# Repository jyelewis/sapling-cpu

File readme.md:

## Sapling CPU

Commands
 - `make test`
 - `make run-sam SAM=pkg6_software/hello.sam`
 - `make run-sam SAM=pkg6_software/primes.sam`

Viewing waveforms
 - `uv run pytest pkg3_cpu_hdl/testbench/test_testbench.py`
 - `surfer build/cocotb/testbench/testbench.fst`

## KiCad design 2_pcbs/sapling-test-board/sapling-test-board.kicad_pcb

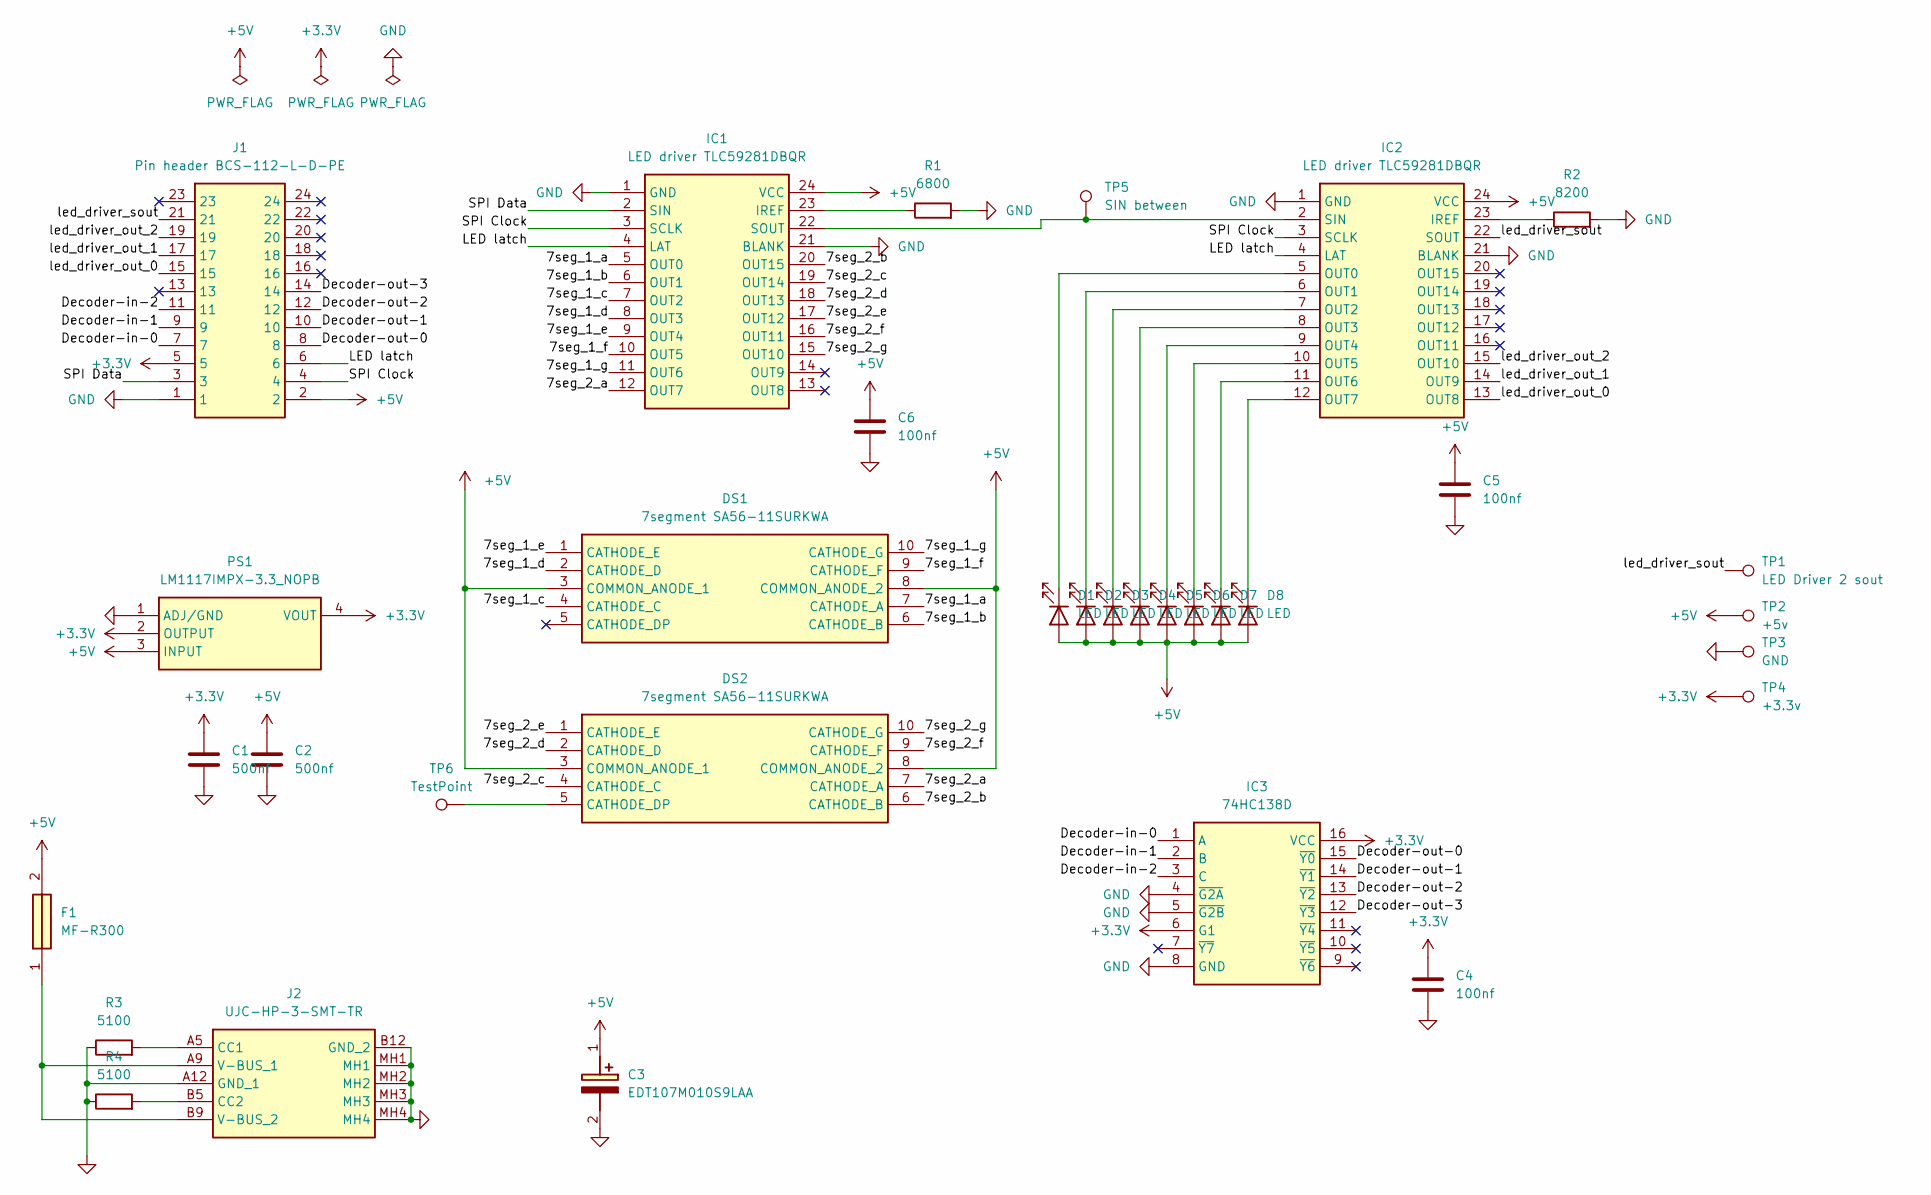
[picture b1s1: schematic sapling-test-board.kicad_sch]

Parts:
C1, C2: 500nf; C_0805_2012Metric
C3: EDT107M010S9LAA; CAPAE830X650N; Mouser Part Number 80-EDT107M010S9LAA
C4, C5, C6: 100nf; C_0805_2012Metric
D1, D2, D3, D4, D5, D6, D7, D8: LED; LED_D5.0mm
DS1, DS2: 7segment SA56-11SURKWA; DIPS1524W75P254L1270H825Q10N; Mouser Part Number 604-SA56-11CGKWA
F1: MF-R300; MFR300; Mouser Part Number 652-MFR300
IC1, IC2: LED driver TLC59281DBQR; SOP64P600X175-24N; Mouser Part Number 595-TLC59281DBQR
IC3: 74HC138D; SOIC127P600X175-16N; Mouser Part Number 757-74HC138D
J1: Pin header BCS-112-L-D-PE; BCS-112-XXX-D-PE; Mouser Part Number 200-BCS112LDPE
J2: UJC-HP-3-SMT-TR; UJCHP3SMTTR; Mouser Part Number 490-UJC-HP-3-SMT-TR
PS1: LM1117IMPX-3.3_NOPB; SOT230P700X180-4N; Mouser Part Number 926-LM1117IMPX33NOPB
R1: 6800; R_0805_2012Metric
R2: 8200; R_0805_2012Metric
R3, R4: 5100; R_0805_2012Metric
TP1: LED Driver 2 sout; TestPoint_Pad_D4.0mm
TP2: +5v; TestPoint_Pad_D4.0mm
TP3: GND; TestPoint_Pad_D4.0mm
TP4: +3.3v; TestPoint_Pad_D4.0mm
TP5: SIN between; TestPoint_Pad_D4.0mm
TP6: TestPoint; TestPoint_Pad_D4.0mm

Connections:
+3.3V: C1.2, C4.2, IC3.6 (G1), IC3.16 (VCC), J1.5, PS1.2 (OUTPUT), PS1.4 (VOUT), TP4.1 (1_1)
+5V: C2.2, C3.1 (+), C5.2, C6.2, D1.2 (A), D2.2 (A), D3.2 (A), D4.2 (A), D5.2 (A), D6.2 (A), D7.2 (A), D8.2 (A), DS1.3 (COMMON_ANODE_1), DS1.8 (COMMON_ANODE_2), DS2.3 (COMMON_ANODE_1), DS2.8 (COMMON_ANODE_2), F1.2, IC1.24 (VCC), IC2.24 (VCC), J1.2, PS1.3 (INPUT), TP2.1 (1_1)
/7seg_1_a: DS1.7 (CATHODE_A), IC1.5 (OUT0)
/7seg_1_b: DS1.6 (CATHODE_B), IC1.6 (OUT1)
/7seg_1_c: DS1.4 (CATHODE_C), IC1.7 (OUT2)
/7seg_1_d: DS1.2 (CATHODE_D), IC1.8 (OUT3)
/7seg_1_e: DS1.1 (CATHODE_E), IC1.9 (OUT4)
/7seg_1_f: DS1.9 (CATHODE_F), IC1.10 (OUT5)
/7seg_1_g: DS1.10 (CATHODE_G), IC1.11 (OUT6)
/7seg_2_a: DS2.7 (CATHODE_A), IC1.12 (OUT7)
/7seg_2_b: DS2.6 (CATHODE_B), IC1.20 (OUT15)
/7seg_2_c: DS2.4 (CATHODE_C), IC1.19 (OUT14)
/7seg_2_d: DS2.2 (CATHODE_D), IC1.18 (OUT13)
/7seg_2_e: DS2.1 (CATHODE_E), IC1.17 (OUT12)
/7seg_2_f: DS2.9 (CATHODE_F), IC1.16 (OUT11)
/7seg_2_g: DS2.10 (CATHODE_G), IC1.15 (OUT10)
/Decoder-in-0: IC3.1 (A), J1.7
/Decoder-in-1: IC3.2 (B), J1.9
/Decoder-in-2: IC3.3 (C), J1.11
/Decoder-out-0: IC3.15 (~Y0), J1.8
/Decoder-out-1: IC3.14 (~Y1), J1.10
/Decoder-out-2: IC3.13 (~Y2), J1.12
/Decoder-out-3: IC3.12 (~Y3), J1.14
/LED latch: IC1.4 (LAT), IC2.4 (LAT), J1.6
/SPI Clock: IC1.3 (SCLK), IC2.3 (SCLK), J1.4
/SPI Data: IC1.2 (SIN), J1.3
/led_driver_out_0: IC2.13 (OUT8), J1.15
/led_driver_out_1: IC2.14 (OUT9), J1.17
/led_driver_out_2: IC2.15 (OUT10), J1.19
/led_driver_sout: IC2.22 (SOUT), J1.21, TP1.1 (1_1)
GND: C1.1, C2.1, C3.2 (-), C4.1, C5.1, C6.1, IC1.1 (GND), IC1.21 (BLANK), IC2.1 (GND), IC2.21 (BLANK), IC3.4 (~G2A), IC3.5 (~G2B), IC3.8 (GND), J1.1, J2.A12 (GND_1), J2.B12 (GND_2), J2.MH1, J2.MH2, J2.MH3, J2.MH4, PS1.1 (ADJ/GND), R1.2, R2.2, R3.1, R4.1, TP3.1 (1_1)
unnamed: D1.1 (K), IC2.5 (OUT0)
unnamed: D2.1 (K), IC2.6 (OUT1)
unnamed: D3.1 (K), IC2.7 (OUT2)
unnamed: D4.1 (K), IC2.8 (OUT3)
unnamed: D5.1 (K), IC2.9 (OUT4)
unnamed: D6.1 (K), IC2.10 (OUT5)
unnamed: D7.1 (K), IC2.11 (OUT6)
unnamed: D8.1 (K), IC2.12 (OUT7)
unnamed: DS2.5 (CATHODE_DP), TP6.1 (1_1)
unnamed: IC1.23 (IREF), R1.1
unnamed: IC1.22 (SOUT), IC2.2 (SIN), TP5.1 (1_1)
unnamed: IC2.23 (IREF), R2.1
unnamed: J2.A5 (CC1), R3.2
unnamed: J2.B5 (CC2), R4.2
unnamed: F1.1, J2.A9 (V-BUS_1), J2.B9 (V-BUS_2)

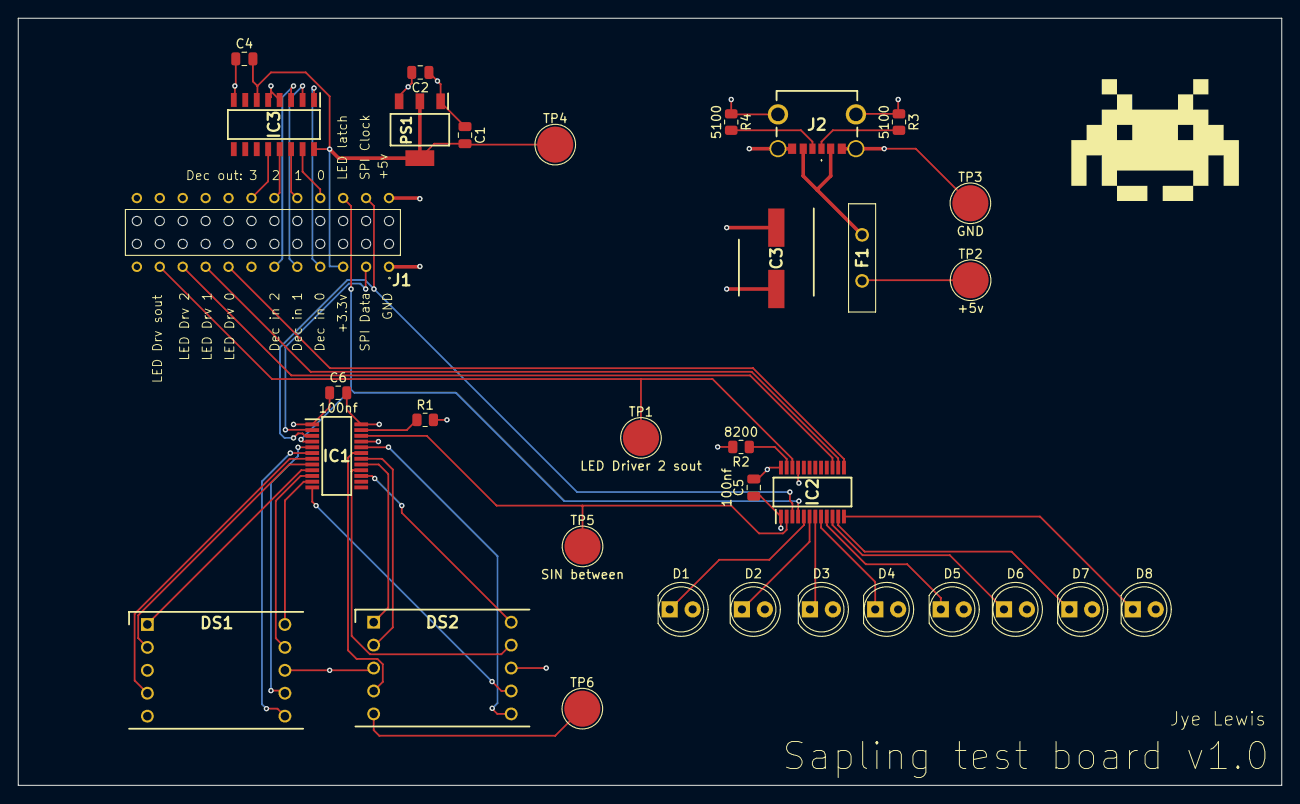
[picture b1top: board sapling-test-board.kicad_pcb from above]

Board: 4 copper layers, 140.0 x 85.0 mm, 33 parts (0 on the bottom side), 46 nets.

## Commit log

2026-04-19 ICEsugar top file & flash commands
2026-04-19 Structure to program different boards with unique IO
2026-04-19 Module: IceSugar_pmod_LEDs
2026-04-19 Module: clock_divider
2026-04-19 Tests
2026-04-19 Cleaned up clock divider edge cases
2026-04-19 SB_GB, github actions
2026-04-20 Components test board
2026-04-20 Auto routed PCB
2026-04-22 Hand routed PCB
2026-04-22 BB PCB review
2026-04-22 ISA instruction segments
2026-04-22 ISA documentation
2026-04-22 Documentation review + tidy up
2026-04-22 Silkscreen
2026-04-22 Test board PCB ordered
2026-04-23 Super basic assembler
2026-04-23 Assembler file outputs
2026-04-23 This is claudes codebase now
2026-04-23 Implement carry modes into assembler
2026-04-23 Implement carry modes into vm
2026-04-23 Another SAM example file
2026-04-23 Clean up the assembler & vm
2026-04-23 Clean up project structure, support #includes
2026-04-23 Break .PHONY blocks apart in makefile
2026-04-23 fmt, move into prefixed sub-dirs
2026-04-23 Remove custom pytest paths
2026-04-25 sapling_cpu_core module & minimal testbench
2026-04-25 Clean up, memory interface needs more thought
2026-04-26 Clean up tb_memory_controller tests
2026-04-26 tb_memory_controller
2026-04-26 Disable TB waves until we can solve for block memory
2026-04-26 test tb_memory_controller writes
2026-04-26 program_counter, test utils
2026-04-26 Fix closure bugs
2026-04-26 More test util clean up
2026-04-26 custom defines in tests, dramatically sped up tb_memory_controller by using packed arrays
2026-04-26 tb_memory_controller is now clocked
2026-04-26 Instruction register
2026-04-26 Instruction decoder
2026-04-26 types package
2026-04-26 Lots-o-wiring-up
2026-04-26 show_waveform() test decorator
2026-04-26 Respect memory stalls
2026-04-26 Always keep next_pc ahead so we're always fetching instructions
2026-04-26 Register bank
2026-04-27 Successfully loading imm8s
2026-04-27 Executing NOPs on FPGA
2026-04-27 VM endianness comments
2026-04-27 LOAD_REG_REG instruction
2026-04-27 Pretty messy but moving towards control signals, also load_reg_reg now works
2026-04-27 Disable waveform in test
2026-04-28 comments
2026-04-28 Split more cleanly into 3 pipeline stages
2026-04-28 Remove old comments
2026-04-28 LOAD_REG_MEM_ABSOLUTE instruction, first microcode step
2026-04-28 Clean up control unit
2026-04-29 STORE_MEM_ABSOLUTE_REG - broken
2026-04-29 STORE_MEM_ABSOLUTE_REG - fixed
2026-04-29 Scaffold ALU
2026-05-02 Complete ALU (not integrated yet)
2026-05-02 Test board pin out
2026-05-03 Messy but functional test board controller
2026-05-03 Integrate ALU, implement ADD opcode (no carry)
2026-05-03 Implement ALU carry
2026-05-04 Implement the rest of the ALU ops, SP relative writes, find problems in pipeline when microcode stalling
2026-05-04 Memory operations now take 3 cycles, until we can work out how to keep the pipeline in place during stalls
